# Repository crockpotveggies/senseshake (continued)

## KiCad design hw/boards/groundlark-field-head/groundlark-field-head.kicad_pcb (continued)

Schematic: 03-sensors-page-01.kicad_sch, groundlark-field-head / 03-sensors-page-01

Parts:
C4, C5, C9: 100n; Capacitor_SMD__C_0603_1608Metric; MPN GRM188R71H104KA93D
R5: 100k; Resistor_SMD__R_0603_1608Metric; MPN RC0603FR-07100KL
R7, R8: 4.7k; Resistor_SMD__R_0603_1608Metric; MPN RC0603FR-074K7L
U2: RM3100 XYZ; Groundlark__PNI_14190_Module; MPN PNI 14190
U3: DLVR-F50D option; Groundlark__DLVR_E1BS; MPN DLVR-F50D-E1BS-I-NI3F; not fitted
U5: TPS22919; Package_TO_SOT_SMD__SOT-363_SC-70-6; MPN TPS22919DCKR

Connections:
6: U2.6 (NC)
GND: C4.2, C5.2, C9.2, R5.2, U2.2 (SA1), U2.4 (SA0), U2.7 (AVSS), U2.14 (DVSS), U3.1 (GND), U5.2 (GND); also elsewhere on the board
MAG_DRDY: U2.5 (DRDY); also elsewhere on the board
SCL: R8.1, U2.1 (SCL), U3.4 (SCL); also elsewhere on the board
SDA: R7.1, U2.3 (SDA), U3.3 (SDA); also elsewhere on the board
SENSOR_EN: R5.1, U5.3 (ON); also elsewhere on the board
V3: C9.1, U5.1 (IN); also elsewhere on the board
V3_SENSOR: C4.1, C5.1, R7.2, R8.2, U2.10 (I2CEN), U2.12 (DVDD), U2.13 (AVDD), U3.2 (VS_3V3), U5.5 (QOD), U5.6 (OUT)
u2-8: U2.8 (NC)
u2-9: U2.9 (NC)
u2-11: U2.11 (NC)
u5-4: U5.4 (NC)

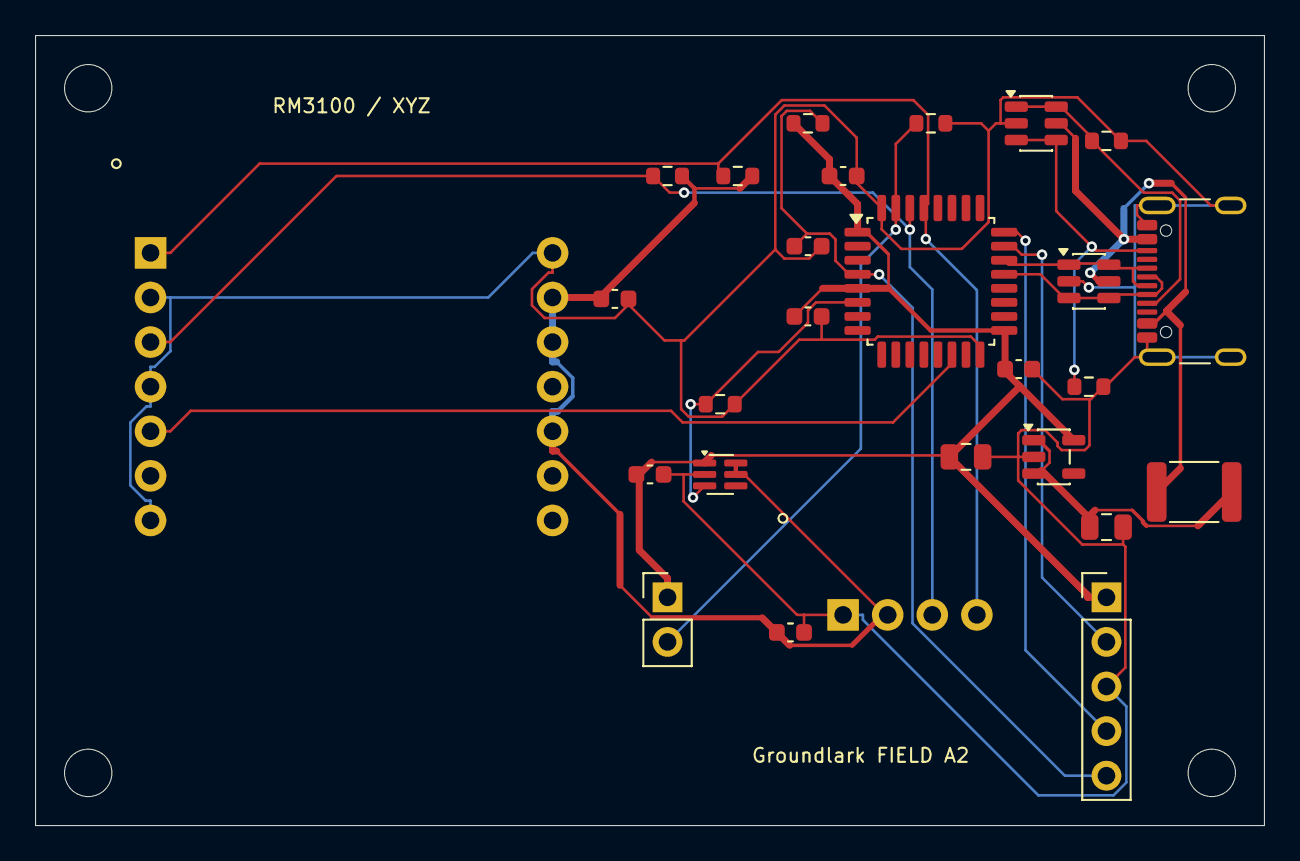
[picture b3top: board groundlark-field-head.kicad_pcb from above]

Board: 4 copper layers, 70.0 x 45.0 mm, 31 parts (0 on the bottom side), 17 nets.

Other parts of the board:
H1, H2, H3, H4: M2.5 NPTH; MountingHole__MountingHole_2.7mm_M2.5

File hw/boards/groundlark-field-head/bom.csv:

Reference,Value,MPN,Footprint,DNP,Note
J1,USB-C DEVICE,USB4105-GF-A,Connector_USB__USB_C_Receptacle_GCT_USB4105-xx-A_16P_TopMnt_Horizontal,False,
R1,5.1k,RC0603FR-075K1L,Resistor_SMD__R_0603_1608Metric,False,
R2,5.1k,RC0603FR-075K1L,Resistor_SMD__R_0603_1608Metric,False,
D1,USBLC6-2SC6,USBLC6-2SC6,Package_TO_SOT_SMD__SOT-23-6,False,
D2,USBLC6-2SC6,USBLC6-2SC6,Package_TO_SOT_SMD__SOT-23-6,False,
F1,500mA PTC,MF-MSMF050-2,Fuse__Fuse_1812_4532Metric,False,
U4,AP2112K-3.3,AP2112K-3.3TRG1,Package_TO_SOT_SMD__SOT-23-5,False,
C1,2.2u,GRM21BR71E225KA73L,Capacitor_SMD__C_0805_2012Metric,False,
C2,4.7u,GRM21BR71A475KA73L,Capacitor_SMD__C_0805_2012Metric,False,
U1,STM32F042K6T6,STM32F042K6T6,Package_QFP__LQFP-32_7x7mm_P0.8mm,False,
C3,100n,GRM188R71H104KA93D,Capacitor_SMD__C_0603_1608Metric,False,
C6,100n,GRM188R71H104KA93D,Capacitor_SMD__C_0603_1608Metric,False,
C7,100n,GRM188R71H104KA93D,Capacitor_SMD__C_0603_1608Metric,False,
C8,100n,GRM188R71H104KA93D,Capacitor_SMD__C_0603_1608Metric,False,
R3,10k,RC0603FR-0710KL,Resistor_SMD__R_0603_1608Metric,False,
R4,10k,RC0603FR-0710KL,Resistor_SMD__R_0603_1608Metric,False,
J2,SWD / 3V3 SENSE,M20-9990545,Connector_PinHeader_2.54mm__PinHeader_1x05_P2.54mm_Vertical,False,Pin 1 is target voltage sense; do not externally power the rail
J3,BOOT0 jumper,EEPROM write enable,Connector_PinHeader_2.54mm__PinHeader_1x02_P2.54mm_Vertical,False,
U5,TPS22919,TPS22919DCKR,Package_TO_SOT_SMD__SOT-363_SC-70-6,False,
R5,100k,RC0603FR-07100KL,Resistor_SMD__R_0603_1608Metric,False,
C9,100n,GRM188R71H104KA93D,Capacitor_SMD__C_0603_1608Metric,False,
R7,4.7k,RC0603FR-074K7L,Resistor_SMD__R_0603_1608Metric,False,
R8,4.7k,RC0603FR-074K7L,Resistor_SMD__R_0603_1608Metric,False,
U2,RM3100 XYZ,PNI 14190,Groundlark__PNI_14190_Module,False,
C4,100n,GRM188R71H104KA93D,Capacitor_SMD__C_0603_1608Metric,False,
U3,DLVR-F50D option,DLVR-F50D-E1BS-I-NI3F,Groundlark__DLVR_E1BS,True,
C5,100n,GRM188R71H104KA93D,Capacitor_SMD__C_0603_1608Metric,False,
H1,M2.5 NPTH,M2.5 NPTH,MountingHole__MountingHole_2.7mm_M2.5,False,
H2,M2.5 NPTH,M2.5 NPTH,MountingHole__MountingHole_2.7mm_M2.5,False,
H3,M2.5 NPTH,M2.5 NPTH,MountingHole__MountingHole_2.7mm_M2.5,False,
H4,M2.5 NPTH,M2.5 NPTH,MountingHole__MountingHole_2.7mm_M2.5,False,

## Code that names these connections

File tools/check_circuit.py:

"""Independent circuit invariants against the actual atopile-compiled PCB."""
from pathlib import Path
import csv,json,re
import pcbnew as p
ROOT=Path(__file__).resolve().parents[1]
def require(pins,ref,expected):
    for pin,net in expected.items():
        assert pins.get((ref,str(pin)))==net,(ref,pin,pins.get((ref,str(pin))),net)
def validate_hat(pins):
    require(pins,'U40',{1:'GND',2:'SENS_3V3',3:'PI_5V'})
    require(pins,'U43',{1:'PI_3V3',2:'PI_I2C_SDA',3:'PI_I2C_SCL',4:'GND',5:'GND',6:'I2C_SCL',7:'I2C_SDA',8:'SENS_3V3'})
    require(pins,'U51',{1:'CF_UART_TX',2:'GND',3:'PI_3V3',4:'PI_UART_RX',5:'PI_UART_TX',6:'CF_IO_ENABLE',7:'CF_3V3',8:'CF_UART_DRIVE'})
    require(pins,'U52',{1:'GND',2:'CF_RESET_N',3:'CF_3V3'})
    require(pins,'Q1',{1:'CF_RESET_GATE',2:'GND',3:'CF_RESET_N'})
    require(pins,'U50',{1:'CF_REG_3V3',2:'PI_5V',3:'PI_5V',4:'GND',5:'CF_SW',6:'CF_BST'})
    require(pins,'L1',{1:'CF_SW',2:'CF_REG_3V3'})
    require(pins,'R60',{1:'CF_REG_3V3',2:'CF_3V3'})
    require(pins,'C62',{1:'CF_BST',2:'CF_SW'})

    require(pins,'J1',{1:'PI_3V3',2:'PI_5V',3:'PI_I2C_SDA',5:'PI_I2C_SCL',8:'PI_UART_TX',10:'PI_UART_RX',11:'CF_RESET_GPIO',22:'CF_IO_ENABLE',37:'SENSOR_OE_N'})
    for ref in ['C1','C2','C44','C46','C48','C75']:require(pins,ref,{1:'PI_3V3',2:'GND'})
    for ref in ['C3','C40','C41','C60','C61']:require(pins,ref,{1:'PI_5V',2:'GND'})
    for ref in ['C12','C13','C14','C15','C16','C17','C18','C19','C20','C22','C24','C25','C26','C42','C43','C45','C47','C49']:require(pins,ref,{1:'SENS_3V3',2:'GND'})
    require(pins,'C21',{1:'TILT_AEXT',2:'GND'});require(pins,'C23',{1:'TILT_DEXT',2:'GND'})
    for n in range(63,66):require(pins,f'C{n}',{1:'CF_REG_3V3',2:'GND'})
    for n in list(range(66,75))+[76,77,78,79]:require(pins,f'C{n}',{1:'CF_3V3',2:'GND'})
    require(pins,'Y1',{1:'CF_3V3',2:'GND',3:'CF_MESH_CLK_RAW',4:'CF_3V3'})
    require(pins,'Y2',{1:'CF_3V3',2:'GND',3:'CF_TILE_CLK_RAW',4:'CF_3V3'})
    require(pins,'R67',{1:'CF_MESH_CLK_RAW',2:'CF_MESH_CLK'});require(pins,'R68',{1:'CF_TILE_CLK_RAW',2:'CF_TILE_CLK'})
    for row in csv.DictReader(open(ROOT/'docs/coldfoot-run1-map.csv')):
        if row['connector_pin']=='71' or not row['hat_net']:continue
        require(pins,'J5',{row['connector_pin']:row['hat_net']})
    for ref in ['U41','U42']:require(pins,ref,{1:'PI_3V3',11:'GND',12:'GND',13:'GND',22:'SENSOR_OE_N',23:'SENS_3V3',24:'SENS_3V3'})
    require(pins,'U41',{2:'PI_3V3'});require(pins,'U42',{2:'GND'})

def main():
    metadata=json.loads((ROOT/'layout.json').read_text());source=(ROOT/'elec/parts.ato').read_text()
    blocks={m[1]:m[2] for m in re.finditer(r'^component (\w+):\n(.*?)(?=^component |\Z)',source,re.M|re.S)}
    reports=[]
    for name,meta in metadata.items():
        target='hat' if name.endswith('-hat') else 'field_head';b=p.LoadBoard(str(ROOT/'layout'/target/(target+'.kicad_pcb')))
        pins={(f.GetReference(),pad.GetNumber()):pad.GetNetname() for f in b.GetFootprints() for pad in f.Pads() if pad.GetNumber()}
        for part in meta['parts']:
            if not part['type']:continue
            block=blocks[part['type']]
            assert f'partnumber="{part["mpn"]}"' in block,(part['ref'],'BOM/source MPN mismatch')
            assert f'footprint="{part["local_fp"]}.kicad_mod"' in block,(part['ref'],'BOM/source footprint mismatch')
        if target=='hat':
            validate_hat(pins)
            # Mutation checks prove these invariants detect actual omissions and
            # dangerous domain cross-connections; source/PCB files are untouched.
            for mutation in ['missing_bypass','wrong_supply']:
                bad=pins.copy()
                if mutation=='missing_bypass':del bad[('C77','1')]
                else:bad[('U51','7')]='PI_5V'
                try:validate_hat(bad)
                except AssertionError:pass
                else:raise AssertionError('Mutation escaped: '+mutation)
        else:
            require(pins,'U2',{1:'SCL',2:'GND',3:'SDA',4:'GND',5:'MAG_DRDY',7:'GND',10:'V3_SENSOR',12:'V3_SENSOR',13:'V3_SENSOR',14:'GND'})
            require(pins,'U3',{1:'GND',2:'V3_SENSOR',3:'SDA',4:'SCL'})
            require(pins,'U1',{1:'V3',5:'V3',16:'GND',17:'V3',32:'GND',4:'NRST',6:'SENSOR_EN',14:'MAG_DRDY',21:'USB_DM',22:'USB_DP',23:'SWDIO',24:'SWCLK',29:'SCL',30:'SDA',31:'BOOT0'})
            require(pins,'J1',{'A5':'USB_CC1','B5':'USB_CC2','A6':'USB_DP','B6':'USB_DP','A7':'USB_DM','B7':'USB_DM','A4':'USB_VBUS','A9':'USB_VBUS','B4':'USB_VBUS','B9':'USB_VBUS','A1':'GND','A12':'GND','B1':'GND','B12':'GND','S1':'GND'})
            require(pins,'R1',{1:'USB_CC1',2:'GND'});require(pins,'R2',{1:'USB_CC2',2:'GND'})
            require(pins,'F1',{1:'USB_VBUS',2:'USB_5V'})
            require(pins,'U4',{1:'USB_5V',2:'GND',3:'USB_5V',5:'V3'})
            require(pins,'U5',{1:'V3',2:'GND',3:'SENSOR_EN',5:'V3_SENSOR',6:'V3_SENSOR'})
            require(pins,'R5',{1:'SENSOR_EN',2:'GND'})
            require(pins,'C1',{1:'USB_5V',2:'GND'})
            require(pins,'C8',{1:'NRST',2:'GND'})
            for n in [2,3,6,7,9]:require(pins,f'C{n}',{1:'V3',2:'GND'})
            for n in [4,5]:require(pins,f'C{n}',{1:'V3_SENSOR',2:'GND'})
        reports.append({'board':name,'compiled_pins':len(pins),'source_bom_agreement':'PASS','circuit_invariants':'PASS'})
    result={'boards':reports,'negative_mutations':['missing supervisor bypass rejected','5V on Coldfoot UART VCC rejected']}
    (ROOT/'simulation/circuit-checks.json').write_text(json.dumps(result,indent=2));print(json.dumps(result,indent=2))
if __name__=='__main__':main()

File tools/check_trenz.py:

"""Independent Trenz carrier pin/geometry checks plus KiCad DRC/ERC.

Critical module pin fixture is transcribed from vendor revision-03 schematic
page 6 and mechanical drawing, independently of the atopile authoring script.
"""
from pathlib import Path
from collections import Counter
import json,subprocess,xml.etree.ElementTree as ET
import pcbnew as p
ROOT=Path(__file__).resolve().parents[1];F=ROOT/'hardware/shakesense-trenz-hat';N=F.name
board=p.LoadBoard(str(F/(N+'.kicad_pcb')));compiled=p.LoadBoard(str(ROOT/'layout/trenz_hat/trenz_hat.kicad_pcb'))
def pins(b):return {(f.GetReference(),q.GetNumber()):q.GetNetname() for f in b.GetFootprints() for q in f.Pads() if q.GetNumber()}
bp,cp=pins(board),pins(compiled);assert all(bp.get(k)==n for k,n in cp.items()),'Compiled circuit changed during layout'
fixture={
 'J80':{1:'FPGA_VIN',3:'FPGA_VIN',5:'FPGA_VIN',13:'FPGA_VIN',15:'FPGA_VIN',9:'FPGA_3V3',11:'FPGA_3V3',14:'FPGA_3V3',28:'FPGA_EN1',89:'FPGA_JTAGEN'},
 'J81':{2:'FPGA_VIN',4:'FPGA_VIN',6:'FPGA_VIN',8:'FPGA_VIN',1:'FPGA_3V3',3:'FPGA_3V3',7:'FPGA_3V3',9:'FPGA_3V3',10:'FPGA_3V3',12:'FPGA_3V3',91:'FPGA_3V3',11:'FPGA_UART_RX',13:'FPGA_UART_TX',14:'FPGA_RESET_N',18:'FPGA_CONFIG_RESET_N',93:'JTAG_TMS',95:'JTAG_TDI',97:'JTAG_TDO',99:'JTAG_TCK'}}
checks=0
for ref,m in fixture.items():
    for modulepin,net in m.items():
        carrierpin=modulepin+1 if modulepin%2 else modulepin-1
        assert bp[(ref,str(carrierpin))]==net,(ref,modulepin,net);checks+=1
for pin,net in {1:'JTAG_TMS',2:'JTAG_TDI',3:'JTAG_TDO',4:'JTAG_TCK',5:'GND',6:'FPGA_3V3'}.items():assert bp[('J84',str(pin))]==net
for pin,net in {1:'PI_3V3',2:'PI_5V',4:'PI_5V',8:'PI_UART_TX',10:'PI_UART_RX',11:'FPGA_RESET_GPIO',22:'FPGA_IO_ENABLE'}.items():assert bp[('J1',str(pin))]==net
assert bp[('U51','3')]=='PI_3V3' and bp[('U51','7')]=='FPGA_3V3'
assert bp[('R62','1')]=='FPGA_IO_ENABLE' and bp[('R62','2')]=='GND'
assert bp[('J83','1')]=='EXT_3V3' and bp[('F80','2')]=='FPGA_VIN'
assert len({'PI_5V','PI_3V3','EXT_3V3','FPGA_VIN','FPGA_3V3'} & set(bp.values()))==5
# Shared sensor circuitry must preserve A2 pad connectivity exactly.
base=pins(p.LoadBoard(str(ROOT/'hardware/shakesense-hat/shakesense-hat.kicad_pcb')))
sensor_refs={'U11','U12','U13','U14','U20','U21','U40','U41','U42','U43'}
degrees=Counter(base.values())
for k,n in base.items():
    if k[0] in sensor_refs and degrees[n]>1:assert bp[k]==n,(k,n,bp[k])
fps={f.GetReference():f for f in board.GetFootprints()}
for ref,xy in {'J80':(55,44),'J81':(55,12),'J82':(34,28),'H80':(33,11),'H81':(77,11),'H82':(33,45),'H83':(77,45),'H1':(3.5,3.5),'H2':(61.5,3.5),'H3':(3.5,52.5),'H4':(61.5,52.5)}.items():
    q=fps[ref].GetPosition();assert abs(p.ToMM(q.x)-50-xy[0])<.001 and abs(p.ToMM(q.y)-50-xy[1])<.001,ref
edge=board.GetBoardEdgesBoundingBox();assert abs(p.ToMM(edge.GetWidth())-85)<.1 and abs(p.ToMM(edge.GetHeight())-56)<.1
for num,xy in {'1':(8.38,4.77),'2':(8.38,2.23),'39':(56.64,4.77),'40':(56.64,2.23)}.items():
    q=next(q for q in fps['J1'].Pads() if q.GetNumber()==num).GetPosition()
    assert abs(p.ToMM(q.x)-50-xy[0])<.001 and abs(p.ToMM(q.y)-50-xy[1])<.001
subprocess.run(['kicad-cli','sch','export','netlist','--format','kicadxml','-o',str(F/'schematic-netlist.xml'),str(F/(N+'.kicad_sch'))],check=True,stdout=subprocess.DEVNULL)
tree=ET.parse(F/'schematic-netlist.xml');sp={}
for net in tree.findall('.//nets/net'):
    for node in net.findall('node'):sp[(node.get('ref'),node.get('pin'))]=net.get('name')
degree=Counter(bp.values())
for k,n in bp.items():
    if degree[n]>1:assert sp.get(k)==n,(k,n,sp.get(k))
for kind,extension,check in [('pcb','kicad_pcb','drc'),('sch','kicad_sch','erc')]:
    subprocess.run(['kicad-cli',kind,check,'--format','json','-o',str(F/(check+'.json')),str(F/(N+'.'+extension))],check=True,stdout=subprocess.DEVNULL)
drc=json.loads((F/'drc.json').read_text());erc=json.loads((F/'erc.json').read_text())
er=[v for s in erc['sheets'] for v in s['violations']]
report={'status':'T1 engineering prototype; not fabrication released','outline_mm':[85,56],'compiled_pin_checks':len(cp),'critical_module_pin_checks':checks,'drc_violations':len(drc['violations']),'unconnected_items':len(drc['unconnected_items']),'erc_violations':len(er),'tracks_and_vias':len(board.GetTracks()),'limits':['No FPGA bitstream port or hardware test performed','External regulated 3.3 V supply required; confirm 3.201–3.399 V at module under startup/load','Copper resistance, heating, sensor thermal drift, EMI and physical mating remain unqualified','Pi rendering is conceptual; Trenz rendering uses vendor generic revision-03 STEP']}
(F/'validation.json').write_text(json.dumps(report,indent=2));print(json.dumps(report,indent=2))
assert not drc['violations'] and not drc['unconnected_items'] and not er

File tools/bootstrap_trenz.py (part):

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
part('J83','TZ_POWER','1715721','TerminalBlock_Phoenix','TerminalBlock_Phoenix_MKDS-1,5-2-5.08_1x02_P5.08mm_Horizontal',[137.5,9],{1:'EXT_3V3',2:'GND'},angle=90,note='REGULATED 3.3 V ONLY; current-limited external supply, 3 A initial operating budget')
part('F80','TZ_FUSE','0467005.NR','Fuse','Fuse_1206_3216Metric',[127,4],{1:'EXT_3V3',2:'FPGA_VIN'},note='5 A fast fuse; not reverse-polarity or overvoltage protection')
part('J84','TZ_JTAG','TSW-106-07-G-S','Connector_PinHeader_2.54mm','PinHeader_1x06_P2.54mm_Vertical',[135,22],{1:'JTAG_TMS',2:'JTAG_TDI',3:'JTAG_TDO',4:'JTAG_TCK',5:'GND',6:'FPGA_3V3'},note='Digilent 6-pin JTAG signal order; reference is an output, not a power input')
part('J85','TZ_AUX','TSW-103-07-G-D','Connector_PinHeader_2.54mm','PinHeader_2x03_P2.54mm_Vertical',[111,26],{1:'FPGA_AUX0',2:'GND',3:'FPGA_AUX1',4:'GND',5:'FPGA_AUX2',6:'GND'},note='3.3 V spare I/O; fit cable before stacking')
part('JP80','TZ_JP','TSW-102-07-G-S','Connector_PinHeader_2.54mm','PinHeader_1x02_P2.54mm_Vertical',[87,50],{1:'FPGA_EN1',2:'GND'},note='Fit shunt to DISABLE module; open enables on-board sequence')
part('JP81','TZ_JP','TSW-102-07-G-S','Connector_PinHeader_2.54mm','PinHeader_1x02_P2.54mm_Vertical',[94,50],{1:'FPGA_CONFIG_RESET_N',2:'GND'},note='Fit shunt to request module configuration reset')
for ref,net,xy in [('R80','FPGA_JTAGEN',[123,36]),('R81','FPGA_NOSEQ',[89,40])]:
    body+=f'\n    {ref.lower()} = new P_10\n    trait {ref.lower()} has_designator<designator="{ref}">\n    {ref.lower()}.p1 ~ {net}\n    {ref.lower()}.p2 ~ GND\n'
    template=copy.deepcopy(next(x for x in parts if x['ref']=='R11'));template.update(ref=ref,xy=xy,section='08-trenz-carrier',note='FPGA JTAG selection / spare CPLD control idle pull-down');parts.append(template)
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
